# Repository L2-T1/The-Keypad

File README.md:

# The-Keypad
This is a keypad that is basically a macropad. It has 9 switches, a rotary encoder, a .91 OLED screen, and a XIAO RP2040.

## Images of PCB and Schematics

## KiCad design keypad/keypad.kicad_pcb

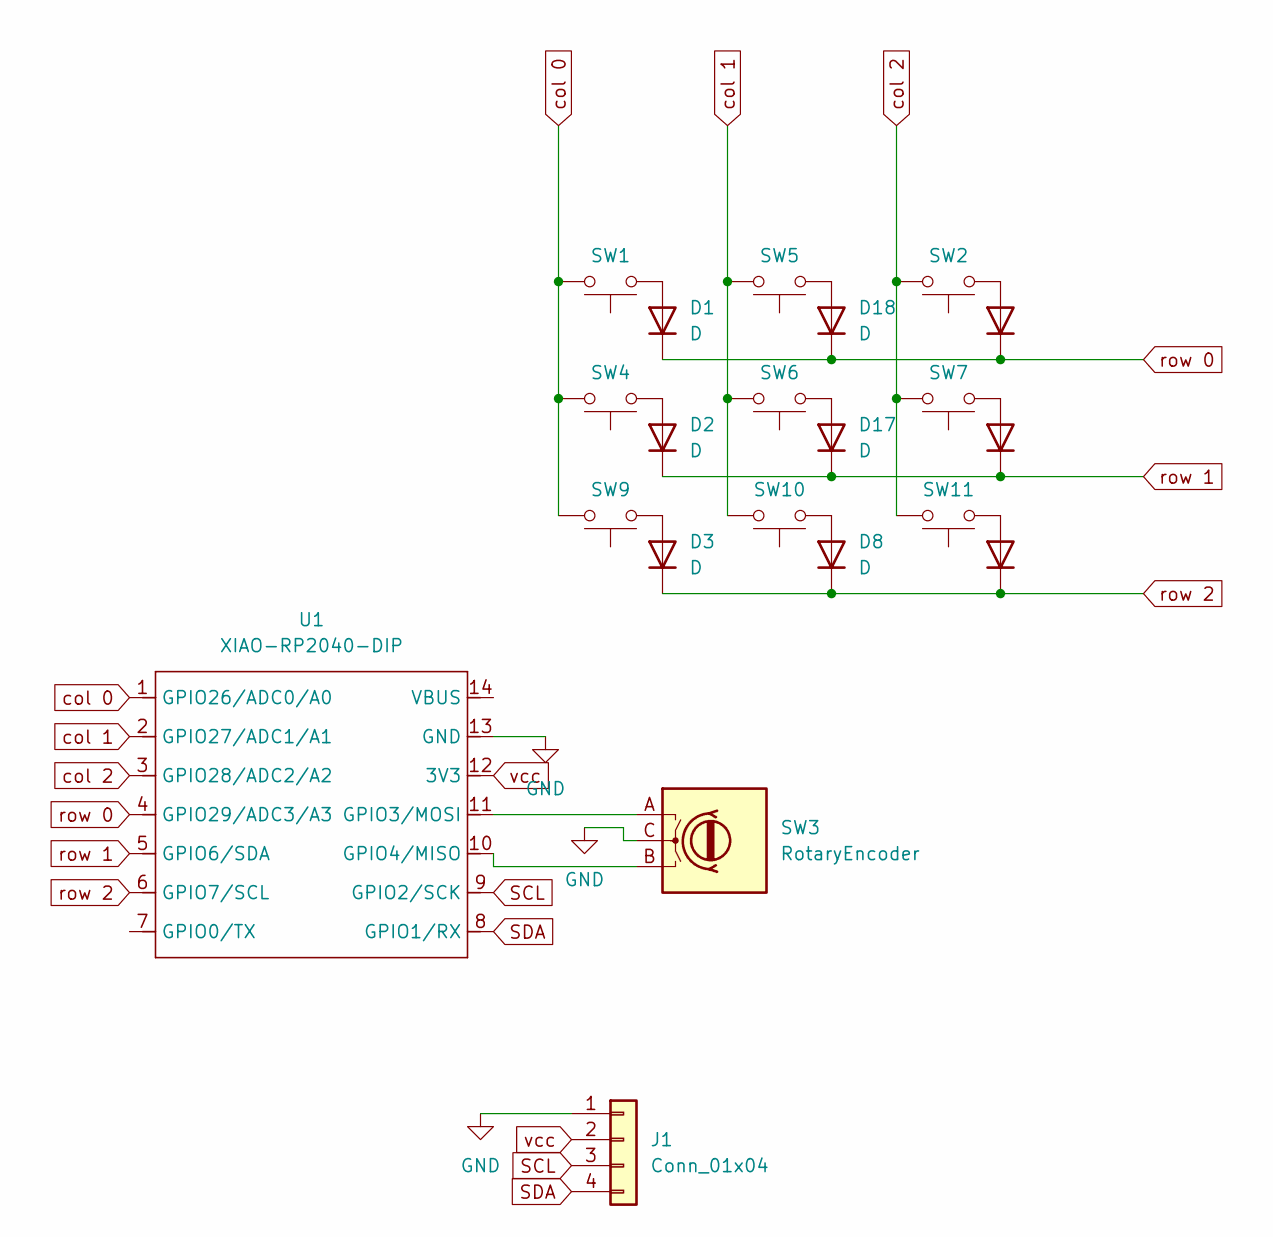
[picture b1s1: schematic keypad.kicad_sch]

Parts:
D1, D2, D3, D8, D13, D16, D17, D18, D19: D; D_DO-35_SOD27_P2.54mm_Vertical_AnodeUp
J1: Conn_01x04; SSD1306-0.91-OLED-4pin-128x32
SW1, SW2, SW4, SW5, SW6, SW7, SW9, SW10, SW11: SW_Push; SW_Cherry_MX_1.00u_PCB
SW3: RotaryEncoder; RotaryEncoder_Alps_EC11E-Switch_Vertical_H20mm_CircularMoun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
U1: XIAO-RP2040-DIP

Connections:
GND: J1.1, SW3.C, U1.13 (GND)
unnamed: D1.2 (A), SW1.1
unnamed: D2.2 (A), SW4.1
unnamed: D3.2 (A), SW9.1
unnamed: D8.2 (A), SW10.1
unnamed: D13.2 (A), SW11.1
unnamed: D16.2 (A), SW7.1
unnamed: D17.2 (A), SW6.1
unnamed: D18.2 (A), SW5.1
unnamed: D19.2 (A), SW2.1
unnamed: SW3.A, U1.11 (GPIO3/MOSI)
unnamed: SW3.B, U1.10 (GPIO4/MISO)
SCL: J1.3, U1.9 (GPIO2/SCK)
SDA: J1.4, U1.8 (GPIO1/RX)
col 0: SW1.2, SW4.2, SW9.2, U1.1 (GPIO26/ADC0/A0)
col 1: SW5.2, SW6.2, SW10.2, U1.2 (GPIO27/ADC1/A1)
col 2: SW2.2, SW7.2, SW11.2, U1.3 (GPIO28/ADC2/A2)
row 0: D1.1 (K), D18.1 (K), D19.1 (K), U1.4 (GPIO29/ADC3/A3)
row 1: D2.1 (K), D16.1 (K), D17.1 (K), U1.5 (GPIO6/SDA)
row 2: D3.1 (K), D8.1 (K), D13.1 (K), U1.6 (GPIO7/SCL)
vcc: J1.2, U1.12 (3V3)

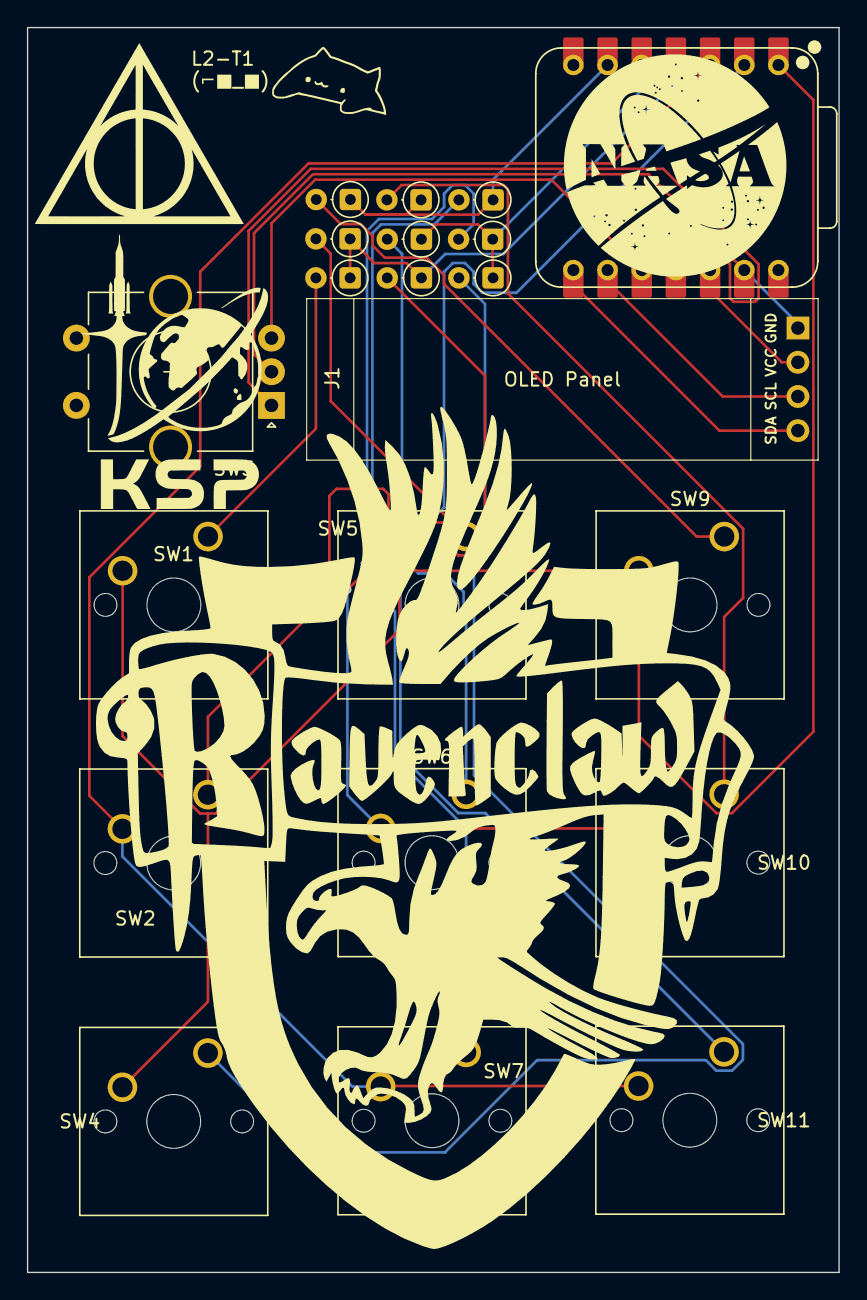
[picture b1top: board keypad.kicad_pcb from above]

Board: 2 copper layers, 60.3 x 92.5 mm, 21 parts (0 on the bottom side), 21 nets.
